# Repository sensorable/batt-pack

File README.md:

# 2P3S Battery Pack
### Designed for use with Sensorable Open Source Cameras

## Specification

* Charging voltage: 14v ... 36v
* Output voltage: 9.3v ... 12.6v
* Batteries: Li-Ion 18650 x3 or x6
* Operational temp: 0C ... 40C
* Enclosure: RP1170
* Water ingress: IP65 with a breathable valve
* Size: 165mm x 86mm x 40mm

## Overview

This battery pack combines several COTS components to allow short production runs with manual assembly. All components are "though-hole" and the whole unit can be ordered and put together by any sufficiently skilled individual. It is not suitable for an automated PCBA process or large production runs.

Charging sources:

* a laptop charger with a barrel connector
* an intermittent power source like street lights, via a transformer
* a solar panel, but the efficiency can be low due to lack of MPPT

**Restarting the pack**

1. Insert the batteries
2. Connect a charger for a brief moment

The BMS requires external voltage close to the pack output to be connected from the outside for it to start working. You need to connect a charger or any similar source of voltage if you removed and re-inserted the batteries.

## Batteries

**Use only high quality Li-Ion 18650 batteries from a trusted manufacturer, e.g. NCR18650B and NCR18650GA from Panasonic.**

The battery holders are connected as 2P-3S, that is, the 2 batteries in the same holder are connected in parallel and the holders are connected in series. This way you can use either 3 or 6 battery cells.

* 3-cell configuration: place one battery into each holder numbered 1,2,3
* 6-cell configuration: fill in all available slots

The charger unit has to be adjusted to the battery type and the size of the pack. Use the 2 blue potentiometers to set the voltage to 4.2v and limit the current to less than 1A, if using NCR18650GA. Check your battery datasheet if using a different type.

The batteries are protected with a commercial BMS module with load balancing. Use only new batteries from the same batch and at exactly the same voltage. The load balancing feature will maintain them in that state, but it will not balance out mismatched batteries.

**BMS spec from the manufacturer datasheet:**
* Charging voltage: 12.6v
* Balance voltage per cell: 4.2v
* Balance current per cell: 42mA
* Max discharge current: 4.5A
* Overcharge protection: 4.35v +/-0.025v
* Overdischarge protection: 2.7v per cell

## Ordering and assembly

1. See the BOM file for the list of components and suppliers
2. We used JLCPCB for making the PCBs with a good result
3. Use cutting and drilling templates from the repo to modify the enclosure

## Enclosure assembly instructions

* Trim the breathable valve by 4mm if placed on the back face under the board. Insert the valve from the inside of the case, tighten the nut back side out, cut off the white plastic flush to the nut.
* Counter-sink post to match the board counter-sinks 
* Mark holes for the switch and PWR IN.
* Check that the holes are marked correctly in relation to the countersunk holes and the vent.

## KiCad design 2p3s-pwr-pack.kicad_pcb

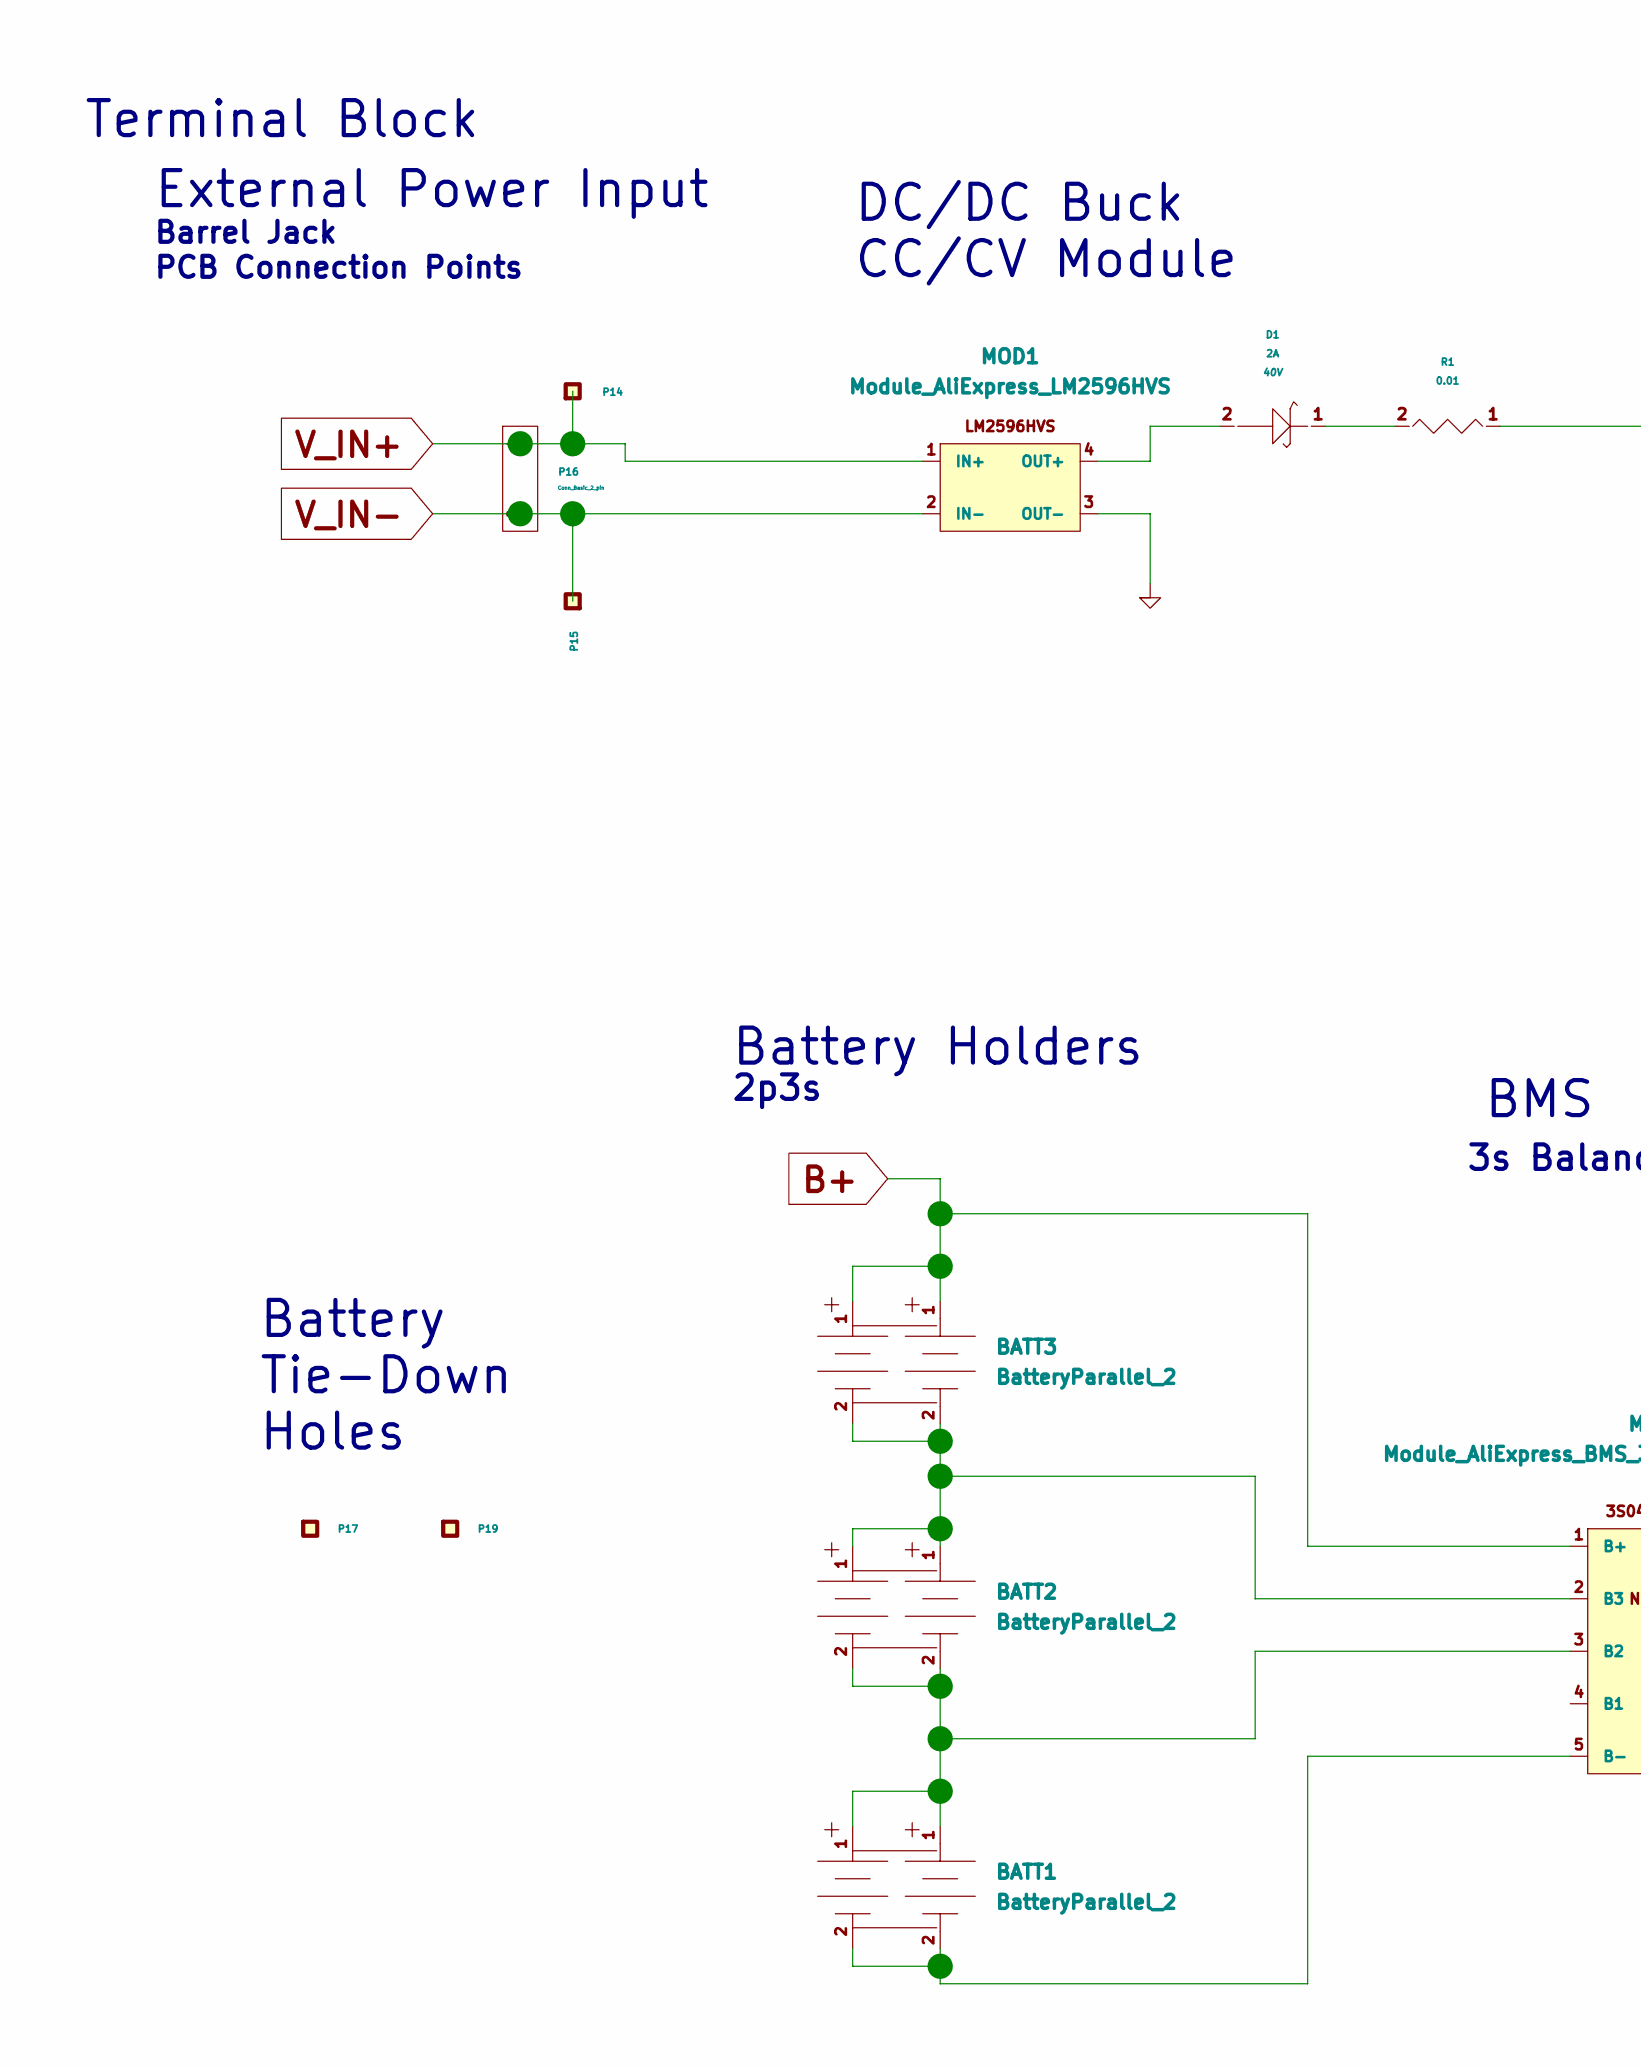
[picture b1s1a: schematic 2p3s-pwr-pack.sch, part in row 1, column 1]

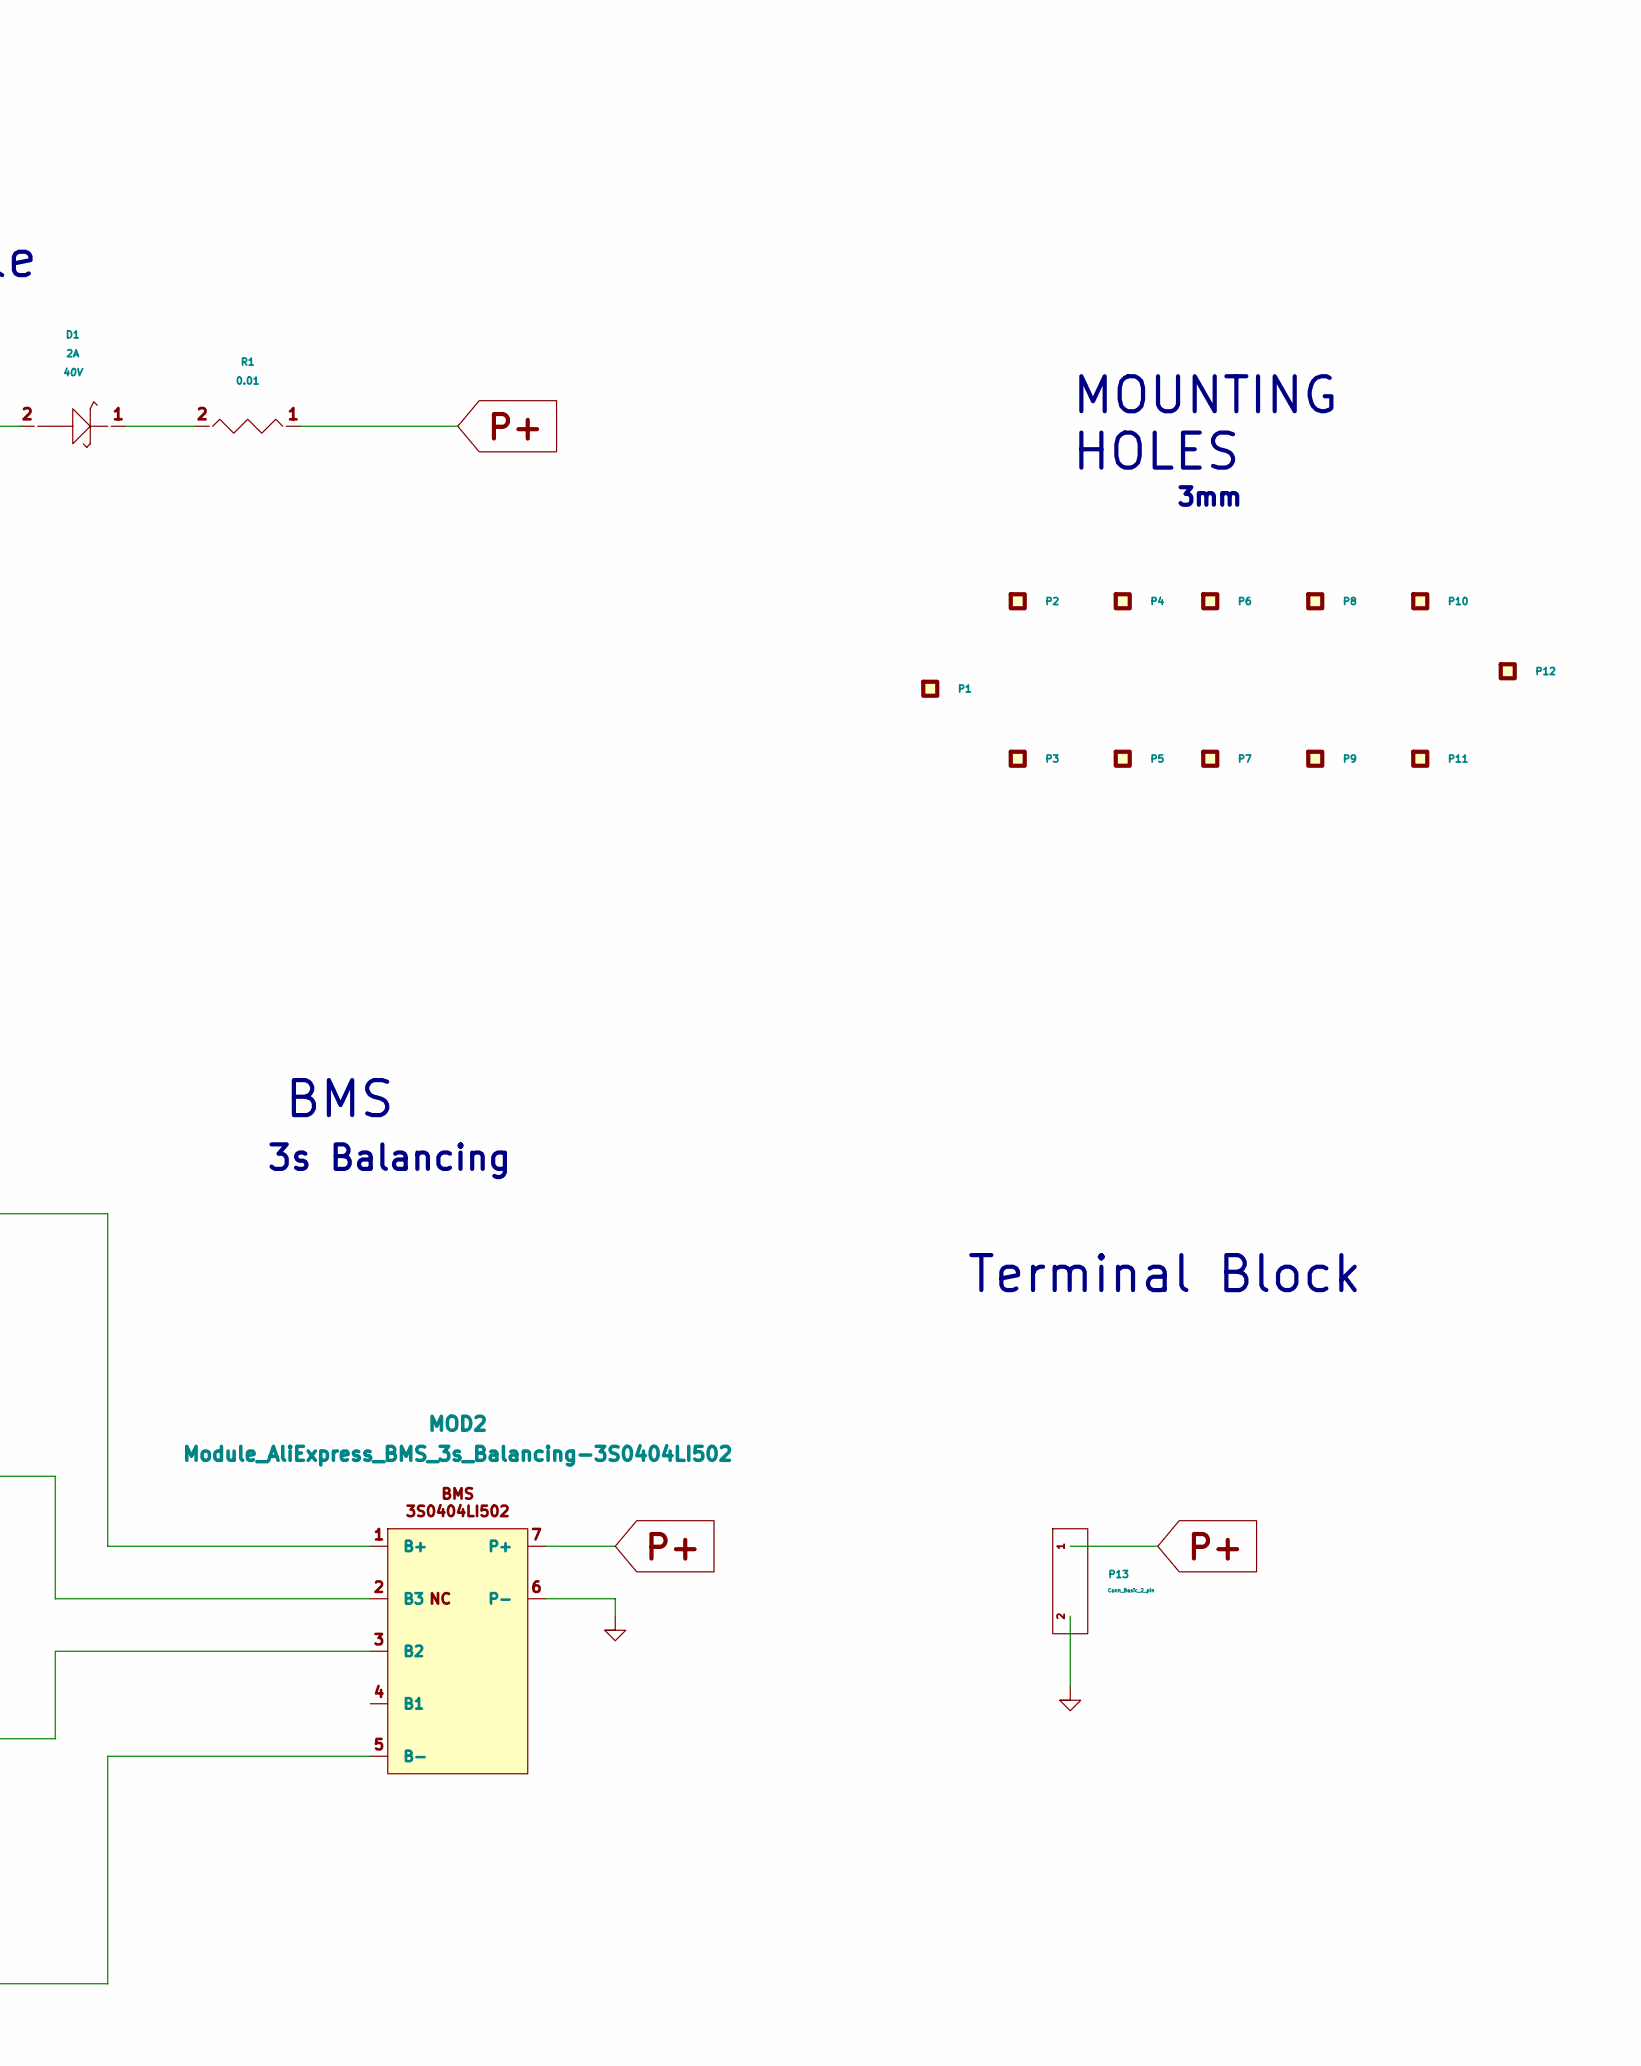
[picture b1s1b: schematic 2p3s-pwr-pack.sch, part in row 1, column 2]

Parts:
BATT1, BATT2, BATT3: BatteryParallel_2; KEYSONE_1049_2x_18650_HOLDER; Manufacturer1PartNumber 1049
D1: 2A; SMA; Voltage 40V; Manufacturer1PartNumber B240AE-13
MOD1: Module_AliExpress_LM2596HVS
MOD2: Module_AliExpress_BMS_3s_Balancing-3S0404LI502; Module_BMS_Balancing_3s_AliExpress_BMS-3S0404LI502; Manufacturer1PartNumber MFG1PN
P1, P2, P3, P4, P5, P6, P7, P8, P9, P10, P11, P12: PAD; NPTH_5mm; Manufacturer1PartNumber MFG1PN
P13, P16: Conn_Basic_2_pin; TERM_BLK_2_SIDE_2.54MM; Manufacturer1PartNumber 1725656
P14, P15: PAD; HOLE_4mmx2.2mm; Manufacturer1PartNumber MFG1PN
P17, P19: PAD; NPTH_3mm; Manufacturer1PartNumber MFG1PN
R1: 0.01; 1206_Medium_Pads; Tolerance 5%; Manufacturer1PartNumber ERJ-8CWJR010V

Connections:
B+: BATT3.1, MOD2.1 (B+)
GND1: MOD1.3 (OUT-), MOD2.6 (P-), P13.2
unnamed: BATT1.1, BATT2.2, MOD2.3 (B2)
unnamed: BATT1.2, MOD2.5 (B-)
unnamed: BATT2.1, BATT3.2, MOD2.2 (B3)
unnamed: D1.1, R1.2
unnamed: D1.2, MOD1.4 (OUT+)
P+: MOD2.7 (P+), P13.1, R1.1
V_IN+: MOD1.1 (IN+), P14.1, P16.1
V_IN-: MOD1.2 (IN-), P15.1, P16.2

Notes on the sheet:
MOUNTING HOLES
3mm
Terminal Block
External Power Input
Barrel Jack
PCB Connection Points
Battery Holders
3s Balancing
BMS
2p3s
DC/DC Buck CC/CV Module
Battery Tie-Down Holes

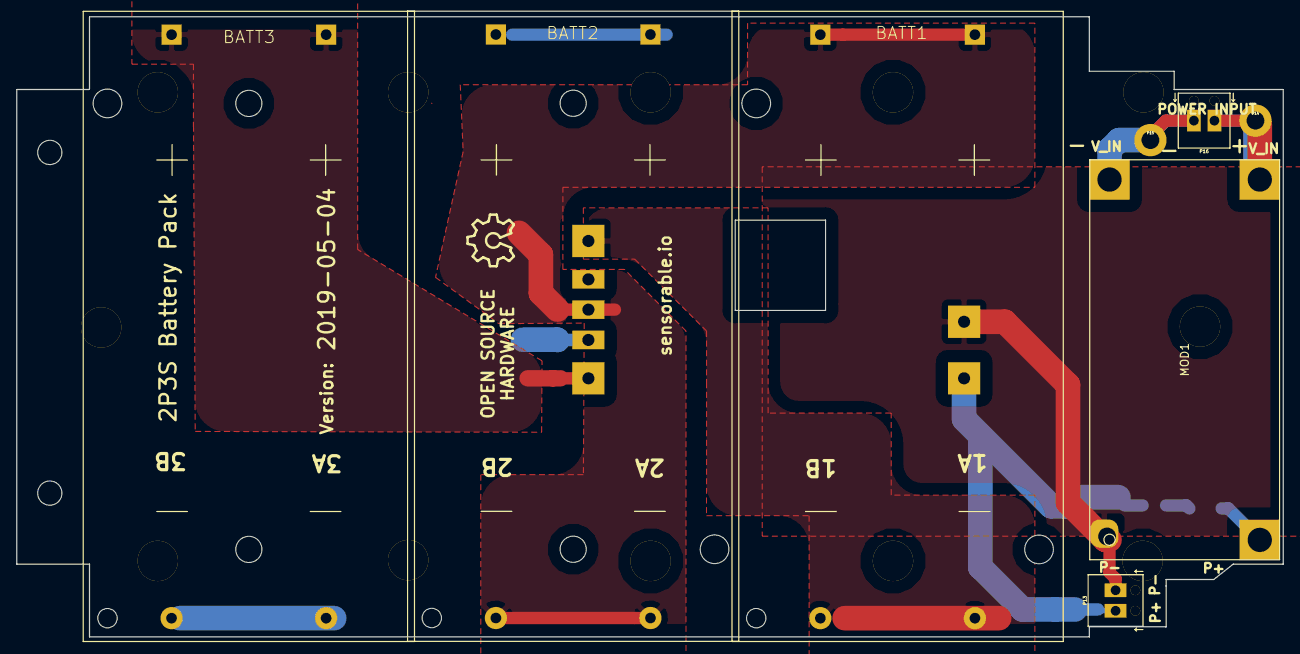
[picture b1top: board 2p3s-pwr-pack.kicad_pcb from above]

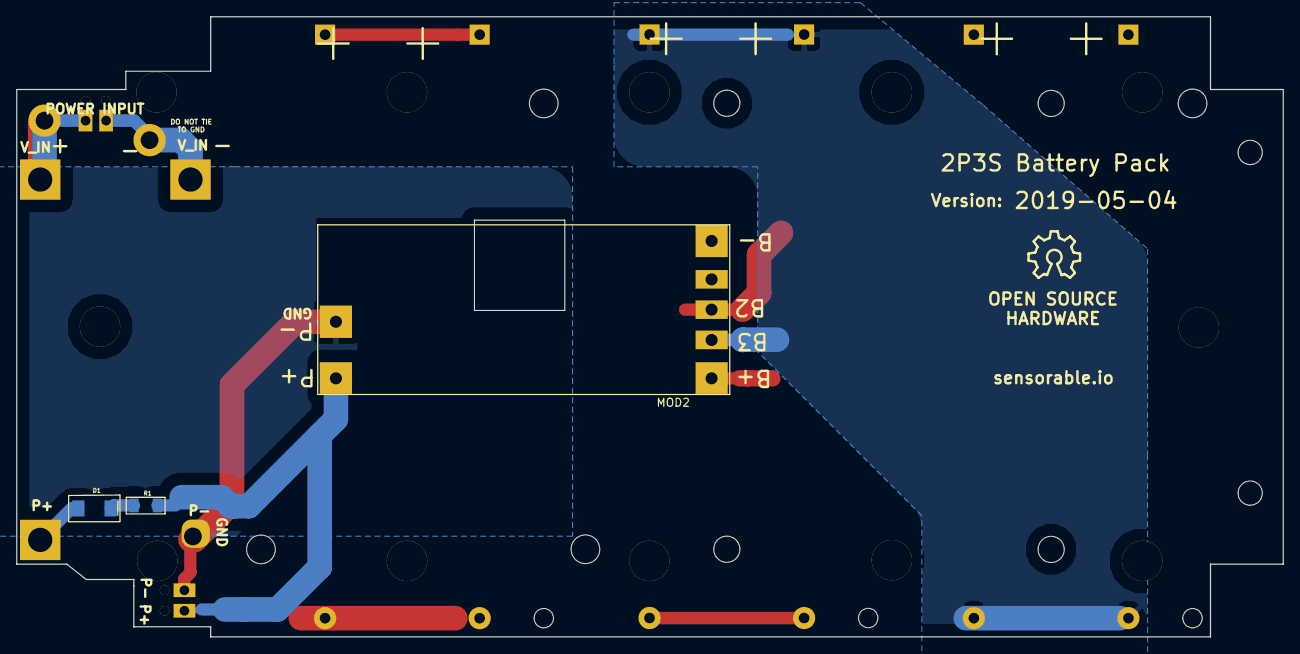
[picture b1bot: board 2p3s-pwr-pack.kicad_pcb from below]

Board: 2 copper layers, 156.8 x 76.8 mm, 25 parts (3 on the bottom side), 10 nets.

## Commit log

2019-03-16 A prorotype for review
2019-03-16 Git LFS fix - added .stl
2019-03-17 2019-03018 ready for ordering.
2019-03-17 Added BOM
2019-03-17 Added basic README
2019-03-24 BOM and Readme updates.
2019-04-09 Missin KiCad files.
2019-04-09 Renamed BOM
2019-04-09 Images for readme.
2019-04-16 Schematic, PCB changes
    Move holder 3 1mm West, holder 2 2mm west, holder 1 3mm west.
    SMA schottky diode on output of CC/CV.
    Fix B1/B3 mixup on BMS
    CC/CV input (-) no longer tied to GND (defeats CC mode)
2019-04-24 Finish JIRA EL-169 changes
    move battery holders, change some holes, add current sensing diode, updates to logo, VIN terminal block
2019-04-30 remove hole in the way
    battery mounting clip in the middle interfered with enclosure stantion boss. removed the battery mounting clip
2019-04-30 Create Sensorable2p3s_Ver30Apr2019_PCB_MFG_Gerbers.zip
    Gerber output for PCB manufacturing (no assembly process on this one).
    Simply upload to SeeedStudio, OSHPark, etc. or forward to PCB manufacturer.
2019-05-03 remove old gerber files
    remove folders containing old gerbers used for verification of the outputs
2019-05-03 PCB ready for manufacture, added mfg files
    Gerber folder containing PDF printouts and gerber outputs of the PCB production data.
    The .zip can be uploaded directly to Seeed/Oshpark/etc. or sent to a PCB manufacturer for PCB manufacturing.
2019-05-03 delete old test gerbers
    delete
2019-05-03 KiCAD design files as in 3May2019 gerber files
    These are the KICAD design files that the may3 gerber outputs were produced from.
2019-05-16 Rename output folder. Track .zip with LFS.
